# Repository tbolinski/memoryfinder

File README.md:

# memoryfinder
A 4 button, 4 led memory game with a twist

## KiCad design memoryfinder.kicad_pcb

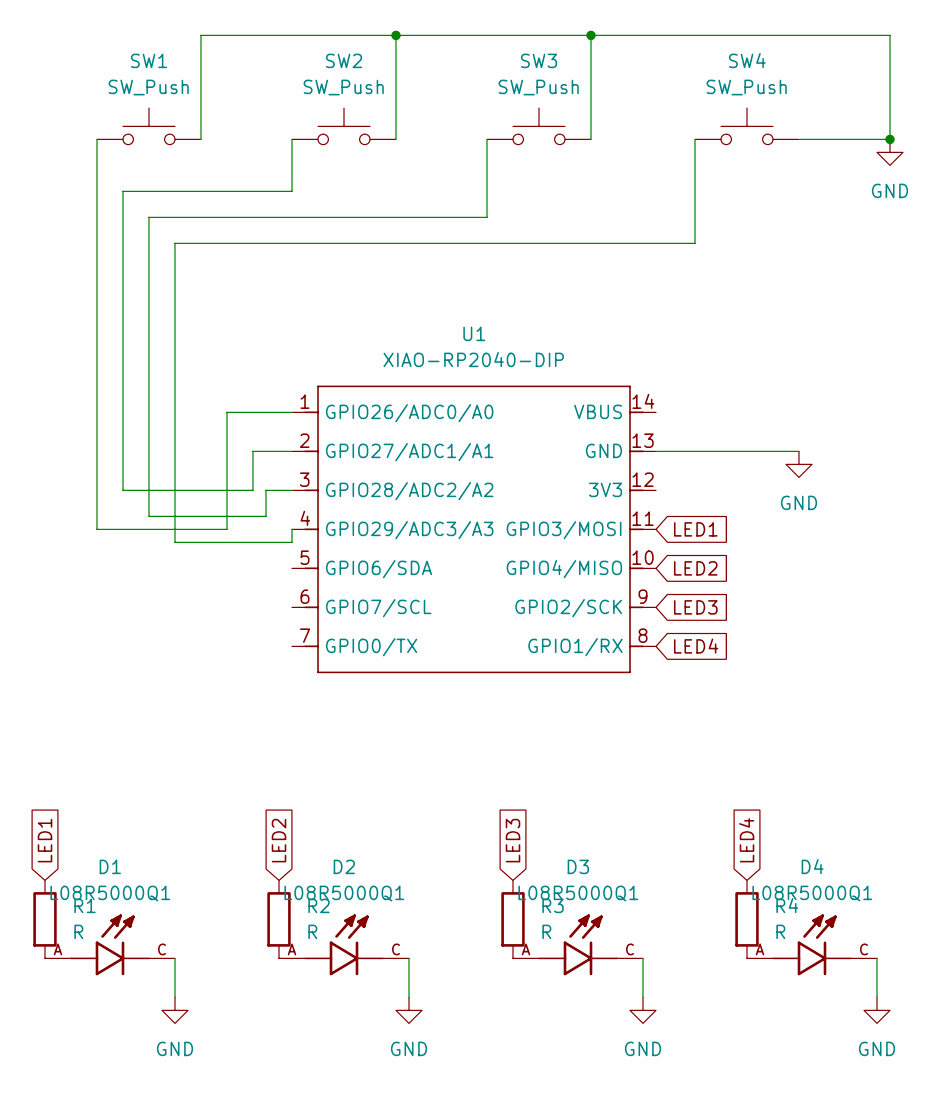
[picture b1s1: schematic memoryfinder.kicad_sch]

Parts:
D1, D2, D3, D4: L08R5000Q1; LEDRD254W57D500H1070; PARTREV NA
R1, R2, R3, R4: R; R_Axial_DIN0204_L3.6mm_D1.6mm_P5.08mm_Horizontal
SW1, SW2, SW3, SW4: SW_Push; SW_Cherry_MX_1.00u_PCB
U1: XIAO-RP2040-DIP

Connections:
GND: D1.C, D2.C, D3.C, D4.C, SW1.2, SW2.2, SW3.2, SW4.2, U1.13 (GND)
LED1: R1.1, U1.11 (GPIO3/MOSI)
LED2: R2.1, U1.10 (GPIO4/MISO)
LED3: R3.1, U1.9 (GPIO2/SCK)
LED4: R4.1, U1.8 (GPIO1/RX)
unnamed: D1.A, R1.2
unnamed: D2.A, R2.2
unnamed: D3.A, R3.2
unnamed: D4.A, R4.2
unnamed: SW1.1, U1.1 (GPIO26/ADC0/A0)
unnamed: SW2.1, U1.2 (GPIO27/ADC1/A1)
unnamed: SW3.1, U1.3 (GPIO28/ADC2/A2)
unnamed: SW4.1, U1.4 (GPIO29/ADC3/A3)

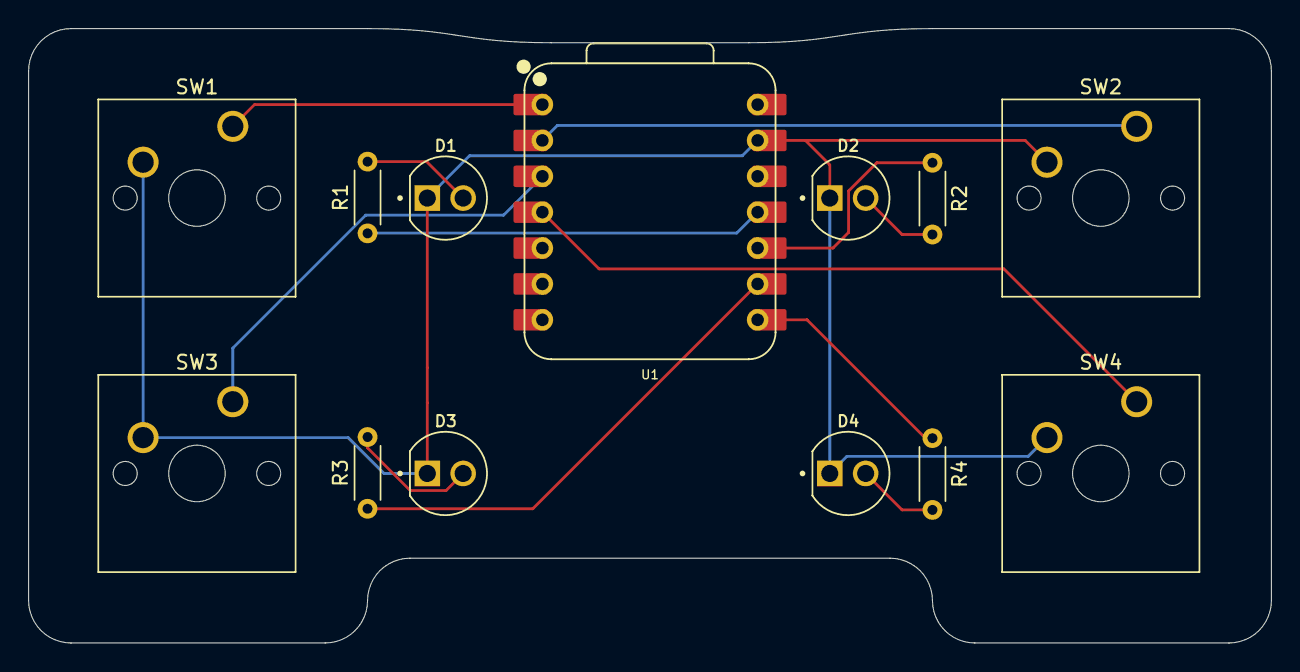
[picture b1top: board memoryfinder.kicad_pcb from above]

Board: 2 copper layers, 88.0 x 43.5 mm, 13 parts (0 on the bottom side), 13 nets.

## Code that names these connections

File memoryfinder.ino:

const int button1 = D0;
const int button2 = D1;
const int button3 = D2;
const int button4 = D3;

const int led1 = D10;
const int led2 = D9;
const int led3 = D8;
const int led4 = D7;

unsigned char maxSequenceLength = 0;
bool doubleGame = false;

void setup() {
  randomSeed(analogRead(0));

  // Init leds
  pinMode(led1, OUTPUT);
  pinMode(led2, OUTPUT);
  pinMode(led3, OUTPUT);
  pinMode(led4, OUTPUT);

  // Init buttons
  pinMode(button1, INPUT_PULLUP);
  pinMode(button2, INPUT_PULLUP);
  pinMode(button3, INPUT_PULLUP);
  pinMode(button4, INPUT_PULLUP);

  // time in milliseconds after the program has started
  unsigned long startTime = millis();
}

void loop() {
  chooseGamemode();
  delay(500);

  if (!doubleGame) {
    unsigned char sequence[maxSequenceLength];
    unsigned char length = 1;

    while (length <= maxSequenceLength) {
      sequence[length - 1] = random(4) + 1;

      for (int i = 0; i < length; i++) {
        flash(sequence[i]);
        delay(250);
      }

      for (int i = 0; i < length; i++) {
        unsigned char input = getButtonPress(10000);
        if (input != sequence[i]) {
          gameOver();
          return;
        }
      }

      length++;
    }
  }
  else {
    bool side = 0;
    unsigned char sequence[2][maxSequenceLength];
    unsigned char length = 1;

    sequence[1][0] = random(4) + 1;

    while (length <= maxSequenceLength) {
      sequence[side][side + length - 1] = random(4) + 1;

      for (int i = 0; i < length; i++) {
        flash(sequence[side][i+side]);
        delay(250);
      }

      for (int i = 0; i < length; i++) {
        unsigned char input = getButtonPress(10000);
        if (input != sequence[!side][i]) {
          gameOver();
          return;
        }
      }
      if (side == 0){
        side = 1;
      }
      else {
        side = 0;
        length++;
      }
    }
  }
  win();
}

void gameOver() {
  for (int i = 0; i < 3; i++) {
    digitalWrite(led1, HIGH);
    digitalWrite(led2, HIGH);
    digitalWrite(led3, HIGH);
    digitalWrite(led4, HIGH);
    delay(200);
    digitalWrite(led1, LOW);
    digitalWrite(led2, LOW);
    digitalWrite(led3, LOW);
    digitalWrite(led4, LOW);
    delay(200);
  }
}

void flash(unsigned char num) {
  const int led = getLed(num);
  digitalWrite(led, HIGH);
  delay(500);
  digitalWrite(led, LOW);
}

int getLed(unsigned char num){
  if (num == 1) {return led1;}
  if (num == 2) {return led2;}
  if (num == 3) {return led3;}
  if (num == 4) {return led4;}
  return led1;
}

unsigned char getButtonPress(unsigned int time) {
  unsigned long startTime = millis();
  while (true) {
    if ((startTime - millis() <= time) && (time != 0)) {
      if (digitalRead(button1) == LOW) {return 1;}
      if (digitalRead(button2) == LOW) {return 2;}
      if (digitalRead(button3) == LOW) {return 3;}
      if (digitalRead(button4) == LOW) {return 4;}
    }
    else {return 0;}
  }
}

void win() {
  for (int i = 0; i < 5; i++) {
    digitalWrite(led1, HIGH);
    delay(100);
    digitalWrite(led1, LOW);
    digitalWrite(led2, HIGH);
    delay(100);
    digitalWrite(led2, LOW);
    digitalWrite(led3, HIGH);
    delay(100);
    digitalWrite(led3, LOW);
    digitalWrite(led4, HIGH);
    delay(100);
    digitalWrite(led4, LOW);
  }
}

void chooseGamemode() {
  digitalWrite(getLed(1), HIGH);
  digitalWrite(getLed(2), HIGH);
  digitalWrite(getLed(3), HIGH);
  digitalWrite(getLed(4), HIGH);

  unsigned char button = getButtonPress(0);

  switch (button) {
    case 1:
      maxSequenceLength = 5;
      doubleGame = false;
      break;
    case 2:
      maxSequenceLength = 15;
      doubleGame = false;
      break;
    case 3:
      maxSequenceLength = 5;
      doubleGame = true;
      break;
    case 4:
      maxSequenceLength = 15;
      doubleGame = true;
      break;
  }

  digitalWrite(getLed(1), LOW);
  digitalWrite(getLed(2), LOW);
  digitalWrite(getLed(3), LOW);
  digitalWrite(getLed(4), LOW);

  delay(250);
  digitalWrite(getLed(button), HIGH);
  delay(500);
  digitalWrite(getLed(button), LOW);
  delay(250);
  digitalWrite(getLed(button), HIGH);
  delay(500);
  digitalWrite(getLed(button), LOW);
  delay(250);
  digitalWrite(getLed(button), HIGH);
  delay(500);
  digitalWrite(getLed(button), LOW);
}

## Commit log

2025-08-01 Added images
2025-08-01 Add KiCAD files
2025-08-01 Add arduino code
